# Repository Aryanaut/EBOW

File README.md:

# EBOW
 Schematics for the EBOW

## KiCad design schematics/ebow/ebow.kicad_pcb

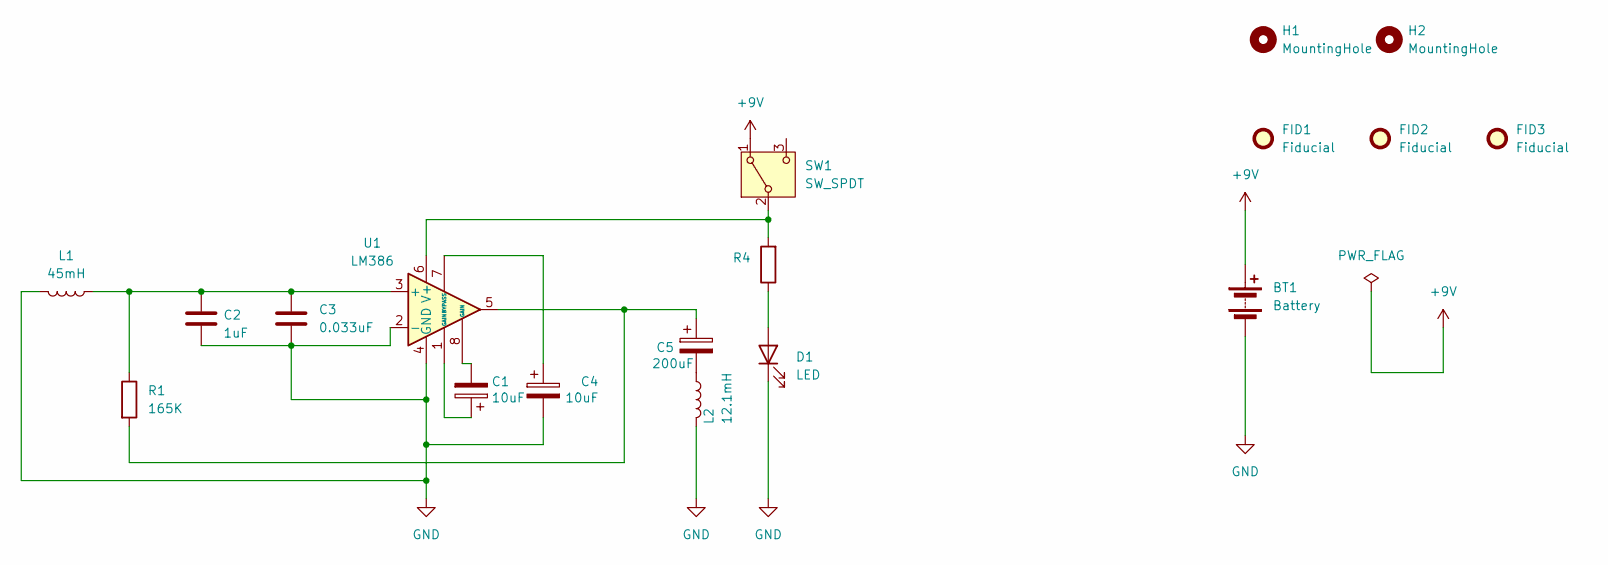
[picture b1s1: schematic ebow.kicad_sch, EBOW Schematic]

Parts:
BT1: Battery; battery_connector_9v
C1, C4: 10uF; CP_Radial_D5.0mm_P2.00mm
C2: 1uF; C_0603_1608Metric
C3: 0.033uF; C_0603_1608Metric
C5: 200uF; CP_Radial_D5.0mm_P2.00mm
D1: LED; LED_D5.0mm_Horizontal_O6.35mm_Z15.0mm
FID1, FID2, FID3: Fiducial; Fiducial_0.5mm_Mask1.5mm
H1, H2: MountingHole; MountingHole_2.1mm
L1: 45mH; Inductor
L2: 12.1mH; Inductor
R1: 165K; R_0201_0603Metric_Pad0.64x0.40mm_HandSolder
R4: 1K; R_0201_0603Metric_Pad0.64x0.40mm_HandSolder
SW1: SW_SPDT; switch-2-mode
U1: LM386; lm386-smd

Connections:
+9V: BT1.1 (+), SW1.1 (A)
GND: BT1.2 (-), C2.2, C3.2, C4.2, D1.1 (K), L1.2, L2.2, U1.2 (-), U1.4 (GND)
unnamed: C1.1, U1.1 (GAIN)
unnamed: C1.2, U1.8 (GAIN)
unnamed: C5.1, R1.2, U1.5
unnamed: C5.2, L2.1
unnamed: D1.2 (A), R4.1
unnamed: R4.2, SW1.2 (B), U1.6 (V+)
unnamed: C2.1, C3.1, L1.1, R1.1, U1.3 (+)
unnamed: C4.1, U1.7 (BYPASS)

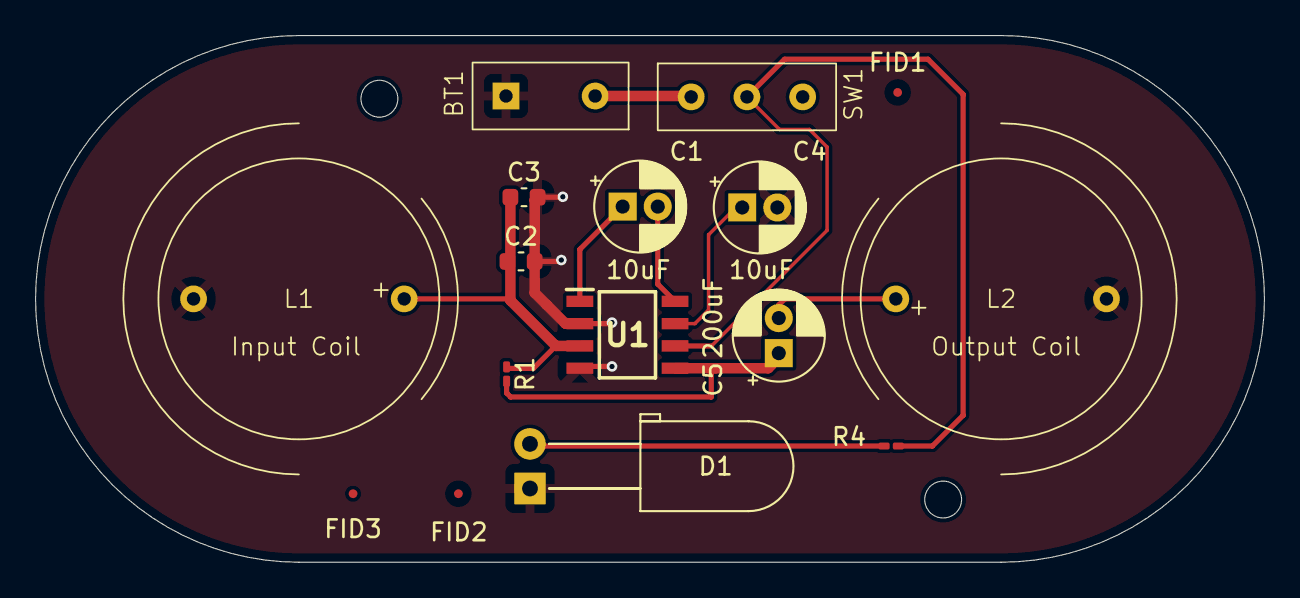
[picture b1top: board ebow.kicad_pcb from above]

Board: 2 copper layers, 70.0 x 30.0 mm, 18 parts (0 on the bottom side), 10 nets.

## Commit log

2025-02-08 ebow schematic without mode switcher
2025-02-10 saving issues
2025-02-10 fixed capacitors, added low and high pass filters, added led indicator
2025-02-10 using inductors to represent coils
2025-02-18 added custom symbol for input and output coils
2025-04-06 completed schematic
2025-06-02 fixed ebow schematic
2025-06-27 added footprints
2025-06-27 first round no routing for pcb
2025-06-29 more edits
2025-07-03 completed first pcb
2025-07-11 corrections
2025-07-11 added footprint library
2025-07-11 more corrections
2025-07-11 updated to fix DRC errors
2025-07-11 fixed ground
2025-07-11 added board characteristics
2025-07-12 fixed vias
